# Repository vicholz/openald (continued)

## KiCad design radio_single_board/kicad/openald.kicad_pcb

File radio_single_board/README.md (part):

# OpenALD: PCB, assembly files and 3D-printed case (v1.0)

OpenALD is an ATmega328PB + RDA5807M (RRD-102 module) FM radio, **programmable over its USB-C port** (CH340K USB-serial, Arduino IDE / MiniCore). It runs from one 18650 cell (reverse-polarity protected), charges over USB-C (TP4056 + DW01A/FS8205A protection) and uses an XC6206 3.3 V LDO. Controls are a thumbwheel encoder with push for volume and tuning (**press the wheel = battery check**; there is no separate battery-check button any more), and a slide power switch that sticks out of the case. A **3-LED battery-level bar** runs as a **vertical column centred across the front face** near the jack end (so it stays well above the rim when the radio stands USB-C-down in the OpenALD Dock), and the TP4056 red/green charge LEDs sit next to the USB-C. The headphone cable acts as the antenna. The board silkscreen reads **OpenALD v1.0**.

> **Note:** I couldn't open the attached spec file on the build machine. This design follows the written summary of the spec instead, so compare it against your original.

> **OpenALD v1.0 is untested hardware.** This release is the former FM radio rev 4.3 design, renamed and reset to v1.0, with no electrical changes. Since then (all still v1.0): the level bar moved to a vertical column near the jack end for the charging dock, and on 2026-11-11 the separate battery-check button SW2 was removed (the wheel press does its job through a small P-FET, Q4) and the bar was centred across the board and moved up (see "Wheel press replaces the battery-check button"). On 2026-11-12 the USB-C receptacle J1 moved 0.9 mm toward the board edge and the case got the Feather's straight cable-plug recess plus assembly notches (see "USB-C 0.9 mm out to the case face"). It passes ERC, DRC and the 3D case-fit check. Pre-release rev 4.2 had two full datasheet reviews, and rev 4.3 (which only changed the charge-current resistor) had its own independent review (see "Pre-release history" below). No board has been built or programmed yet. Build one or two first.

> **t116u (2026-11-24, still v1.0): USB-C on the bottom END, centred — supersedes the side-USB envelope below.**
> Victor: "All boards except for the MI03 should have the USB-C connector in the same location at the bottom so they
> can be placed into the charging station for charging … Try to keep the single board 2 layer."
> * **Board 26.9 × 84.75 mm, still 2 layers** (was 25.5): J1 moved to the **bottom edge, centred** (shell 1.5 mm
>   past the edge); everything re-placed around it (holder + pin now toward the USB end, level bar D1/D5/D6 as a
>   column and the TP4056 charge LEDs D3/D4 at the top / jack end, wheel and switch on the right edge, jack top-left).
>   Re-routed with Freerouting: 983 track segments, 146 vias, 2.11 m; GND pours on both layers.
> * **Case 31.9 W × 89.75 L × 33.86 T** (front shell 9.85, back cover 24.01; thinner than the 34.83 side-USB case).
>   **USB-C in the bottom end face, centred across the width, 6.62 mm behind the front face, mouth 1.0 mm inside
>   the face**, 13.0 × 7.6 r 3 cable-plug recess — identical to the Feather radio, so both stand in the same dock
>   pocket (`../charging_dock/DOCK_INTERFACE.md`). Jack hole in the top end wall. Switch knob 2.8 mm and wheel
>   0.35 mm proud of the right side (above the pocket; t122u: no notch).
> * Checks: ERC 0 errors / 2 accepted warnings; **DRC 0 errors, 0 unconnected**, 82 silk-only (9 edge / 35 over
>   copper / 38 overlap); JLC CPL correction table OK; case fit **0 interferences** (closest LED tunnel: Q1, 0.25 mm).
>   JLC parts ≈ $7.32 / board. Fab outputs, vendor BOMs and previews regenerated.
> * The notes below (side USB-C, 25.5 mm board, 30.5 × 89.75 × 34.83 case) are history.
> * **t122u dock collar:** the Feather case grew to 35.9 wide, so the dock pockets are 35.9 × 33.86 now. This case
>   keeps its 31.9 body but its **lowest 27 mm (the part in the 25 mm pocket) is 35.9 wide**, 2 mm extra per side,
>   with a 2 mm 45° step back to the body (`dock_W`, `dock_collar_h` in `case/openald_case.scad`). The switch knob
>   and wheel are above the collar and unchanged. Outer bounding box 35.9 × 89.75 × 33.86; fit 0 interferences.

> **2026-11-24 unified envelope (still v1.0; supersedes the size, mounting, USB-C, LED and case notes further down,
> which are kept as history).** Victor asked for the single board and the Feather to match the MI03 case so all three
> use one charging dock. Changes:
> * **Board 25.5 × 84.75 mm, 2 layers**, 1.6 mm (was 38 × 87). A first cut at 22.5 mm wide only closed on 4 layers;
>   Victor then asked to make the board and cases "slightly bigger if it helps to keep the board 2 layers", so the
>   board was widened (length unchanged) and parts spread across the extra width (`placement.py`: J1 stays on the
>   left edge, wheel and switch on the right edge, holder centred). Freerouting on 2 layers: **24.5 and 25.0 mm left
>   3 unconnected nets** (U3 SCK/RX/TX area; 24.5 tried twice), **25.5 mm routed completely**, so 25.5 is the
>   smallest width found (0.5 mm steps). GND is routed as copper like every other net, and both layers carry GND
>   pours (islands removed) stitched with vias, so the ground is connected by tracks, not only by the pours. Same
>   schematic, same parts, BH-18650-PC holder kept.
> * **USB-C J1 moved to the left long edge**, centred 27.8 mm below the board's top end = **30.3 mm from the case's
>   top outer end, 7.55 mm behind the front face, mouth 1.0 mm inside the side face** (MI03 values), with the MI03
>   13.0 × 7.6 r 3 cable-plug recess. The radio docks **lying on that side**.
> * **Case 30.5 W × 89.75 L × 34.83 T** (was 43 × 92 × 33.4): same length, thickness, corners (r 5 / r 2) and USB-C
>   position as the MI03 case; 3 mm wider than the MI03 (27.5) because of the 2-layer board. Width is the height above
>   the pocket floor in the dock, so it uses the same pockets.
>   **Thickness grew 1.43 mm (33.4 → 34.83)**: the USB-C must sit 7.55 mm behind the front face like the MI03's,
>   and with the PCB at that depth the front shell is 10.78 mm tall; the holder under the board then needs 24.05 mm
>   behind it. Keeping 33.4 would have meant moving the MI03's USB-C, which Victor gave as the reference.
> * Level bar (D1/D5/D6) is now a row **across** the board near the top end (reads as a vertical bar when docked,
>   well above the pocket rim); the TP4056 charge LEDs D3/D4 sit beside it. Each has its own light tunnel.
> * Mounting: no more corner holes. The holder is screwed through its own two floor holes, a 0.8 mm printed
>   **holder spacer** and the PCB into two front-shell bosses (2 × M2 self-tapping). The **back cover snaps on**
>   (lip + 4 bumps), so the cell is changed without tools. The heat-set inserts and `case/nut_variant/` are gone.
> * Checks: ERC 0 errors / 2 accepted warnings; **DRC 0 errors, 0 unconnected**, 87 cosmetic silkscreen warnings (10
>   silk_edge_clearance, 33 silk_over_copper, 44 silk_overlap); JLC CPL correction table OK; case fit **0
>   interferences** (closest: Q4's LED tunnel, 0.40 mm); all three STLs watertight single bodies. 1360 track segments,
>   167 vias, 2.37 m of track.

The hardware in this v1.0 package is the ~900 mA charge-current design (R3 = 1.2k, TP4056 PROG). Charge time for a 3000 mAh 18650 is about 3.7 h if the chip holds 900 mA through the CC phase, likely closer to ~4 h in the closed case if the TP4056 thermally throttles. Use a **≥ 1 A charger**. A laptop USB 2.0 port is only rated 500 mA. If you need to charge from a laptop USB-A port, change **R3 to 2.4k (C22940, Basic) for ~460 mA**. See the pre-release rev 4.3 notes for the thermal estimate, USB source details, and the first-board cell-temperature check.

## Board at a glance
| | |
|---|---|
| Size | **26.9 x 84.75 mm**, 1.6 mm FR-4, 2 layers, 1 oz, 2.5 mm corner radius (t116u 2026-11-24; was 25.5 x 84.75, before that 38 x 87) |
| Mounting | No corner holes. 2x M2 self-tapping screws through the holder's two floor holes, the spacer and the PCB at (12.75, 17.62) and (12.75, 73.23) mm from the top-left corner into front-shell bosses |
| Top side | All SMT parts (including the 3 level-bar LEDs), plus the power switch (THT) and the hand-soldered RRD-102 module |
| Bottom side | MPD BH-18650-PC holder only (THT, hand-soldered) |
| Copper | 2026-11-24: GND routed by Freerouting like every other net, plus GND pours on F.Cu and B.Cu (islands removed) and stitching vias. Power nets 0.5 mm, signals 0.25 mm (0.15 mm minimum at the TQFP/ESSOP pins). 0.45 mm edge keep-out while routing. 1360 track segments, 167 vias, 2.37 m |
| ERC | **0 errors**, 2 accepted warnings (`fab/erc_report.txt`): pin_to_pin on U3 pins 3/6 (PE0 tied to GND, PE1 tied to +3V3 for ATmega328P-AU drop-in). This is intentional |
| DRC | **0 errors, 0 unconnected pads** (2026-11-24 2-layer re-route). 87 cosmetic silkscreen warnings are waived: 10 silk_edge_clearance (the jack, wheel, switch and USB-C overhang the edge on purpose), 33 silk_over_copper, 44 silk_overlap |

## How charging is shown (power switch off or on)
The power switch cuts VSYS. In rev 4 the MCU also runs from USB with the switch off (see "Power path"), so firmware can show the charging animation on its own while USB is plugged in (optional). The rev 3 options still work:
1. **Always, with no MCU needed:** the TP4056's own LEDs, **D3 red = charging and D4 green = full**, light from USB power. They shine through their own two light tunnels just left of the USB-C. This works with the switch off.
2. **With the switch off, hold the wheel pressed in:** the wheel's push switch turns on P-FET Q4, which powers the MCU from the battery (through D10, and VSYS through D2) for as long as the wheel is held in. While held, the MCU reads nCHRG and shows the charging animation or the level on the bar. Releasing the wheel powers it off again.
3. **With the switch on:** a short press of the wheel any time shows the level on the bar, or the charging animation if USB is charging. Plugging USB in while the radio is on also shows the charging animation once for 3 s.

Rev 4 powers the MCU from USB through its **own** LDO (U6) instead of feeding VBUS into VSYS. That way the FM module and the battery divider stay off. Note that while USB is powering the MCU with the switch off, BAT_ADC reads about 0 V, so the cell voltage isn't measurable then. For the level while charging, hold the wheel in (VSYS then sees the cell through Q4 and D2) or switch on.

## Part colours (t124u)
Victor: "make all 3 cases and their parts different colors so it is easy to tell the parts apart". Each case family has
its own hue (single board **blues**, Feather **greens**, MI03 **oranges / reds**, dock **purples**); this one uses
**blues**. The same colours are used in every preview and in the coloured 3MF plate **`case/openald_single_board_case_colored.3mf`** (all printed parts laid
out on one plate, each a separate named object with its colour; source `../tools/palette.py`, rebuilt by
`../tools/make_3mf.py`). Colours are only for telling the parts apart; print in any filament.

| Part (STL) | What | Colour | Hex |
|---|---|---|---|
| `case/case_top.stl` | front shell | blue | `#2E6FD8` |
| `case/case_bottom.stl` | back cover | light blue | `#9CC3F5` |
| `case/holder_spacer.stl` | holder spacer | navy | `#0B2E6B` |

## Files
```
kicad/                     KiCad 9 project (open openald.kicad_pro)
  openald.kicad_sch       schematic (PDF in docs/openald-schematic.pdf)
  openald.kicad_pcb       routed board
  openald.pretty/         custom footprints: RRD-102 module, Mitsumi SIQ-02FVS3, HRO SK-12E12-G5 switch (U3/U7/U8 use stock KiCad footprints)
  openald.kicad_sym       custom symbols;  openald.3dshapes/  simple 3D models for previews and the fit check
fab/
  openald-gerbers-jlcpcb.zip   Gerbers + Excellon drill files (upload this)
  openald-BOM-jlcpcb.csv       JLC assembly BOM (Comment, Designator, Footprint, LCSC Part #)
  openald-CPL-jlcpcb.csv       JLC pick-and-place (Designator, Mid X, Mid Y, Layer, Rotation), corrected for EasyEDA origins
  openald-centroid.csv         standard centroid / XY file (Designator, Comment, Footprint, Mid X, Mid Y, Rotation, Layer); same positions as the JLC CPL
  openald.pos                  KiCad ASCII position file (mm); same corrected positions as the centroid/CPL, plus hand-soldered U4 and BT1
  jlc_cpl_fit.json              per-part fit of the EasyEDA footprints (offsets, rotations, pad match)
  openald-BOM-human.csv        full BOM with MPNs, qty, live LCSC stock and price, links, plus hand-solder and off-board parts
  openald-BOM-pcbway.xlsx      PCBWay SMT assembly BOM (official template filled; qty per board; title says 5PCS)
  openald-BOM-nextpcb.xls      NextPCB assembly BOM (official template filled; qty per board)
  minimal/                      JLC files for a 4-part "hotplate" assembly only (see below)
    openald-BOM-jlcpcb-minimal.csv
    openald-CPL-jlcpcb-minimal.csv
    openald-centroid-minimal.csv
    openald-minimal.pos
    openald-LCSC-order-handsolder.csv   remaining LCSC parts for 5 boards, with labelled spares
    cost_estimate.txt
  erc_report.txt, drc_report.txt, lcsc_lookup.json, cost_summary.json
case/
  openald_case.scad       parametric OpenSCAD case (includes case_params.scad)
  case_params.scad         AUTO-GENERATED from the PCB by scripts/gen_case_params.py
  case_top.stl             front shell (PCB + holder screw into it)
  case_bottom.stl          snap-on back cover
  holder_spacer.stl        0.8 mm plate between the PCB and the holder
  case_fit_report.txt      3D interference check of the assembled PCB against both halves and the LED tunnel walls
previews/                  pcb_top.png, pcb_bottom.png, pcb_closeup_led_bar.png, pcb_closeup_reverse_polarity.png,
                           pcb_closeup_polarity_marks_bottom.png (rev 4.2), schematic-1.png, case_closed.png, case_*.png,
                           closeup_led_bar.png, closeup_front_usb_leds.png, cutaway_led_tunnels.png (section through the bar),
                           closeup_power_switch.png, closeup_usb_c.png, closeup_thumbwheel.png, closeup_jack_end.png,
                           cpl_overlay_<REF>.png (EasyEDA/JLC footprint vs KiCad pads; rev 4 adds U3/U6/U7/U8, rev 4.2 Q2/Q3, 2026-11-11 Q4),
                           pcb_closeup_usb_serial.png
docs/openald-schematic.pdf
scripts/                   generator scripts. run_all_pcb.sh regenerates everything up to DRC,
                           make_fab.py the fab outputs (add --minimal for the hotplate assembly set),
                           make_vendor_boms.py the PCBWay/NextPCB BOMs (templates in scripts/templates/),
                           build_case.sh the case, its checks and the renders
```

## Ordering at JLCPCB (assembled)
1. Upload `fab/openald-gerbers-jlcpcb.zip`. Settings: 2 layers, 26.9x84.75 mm, 1.6 mm, any colour, HASL (lead-free) or ENIG.
2. Turn on **PCB Assembly**, top side.
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
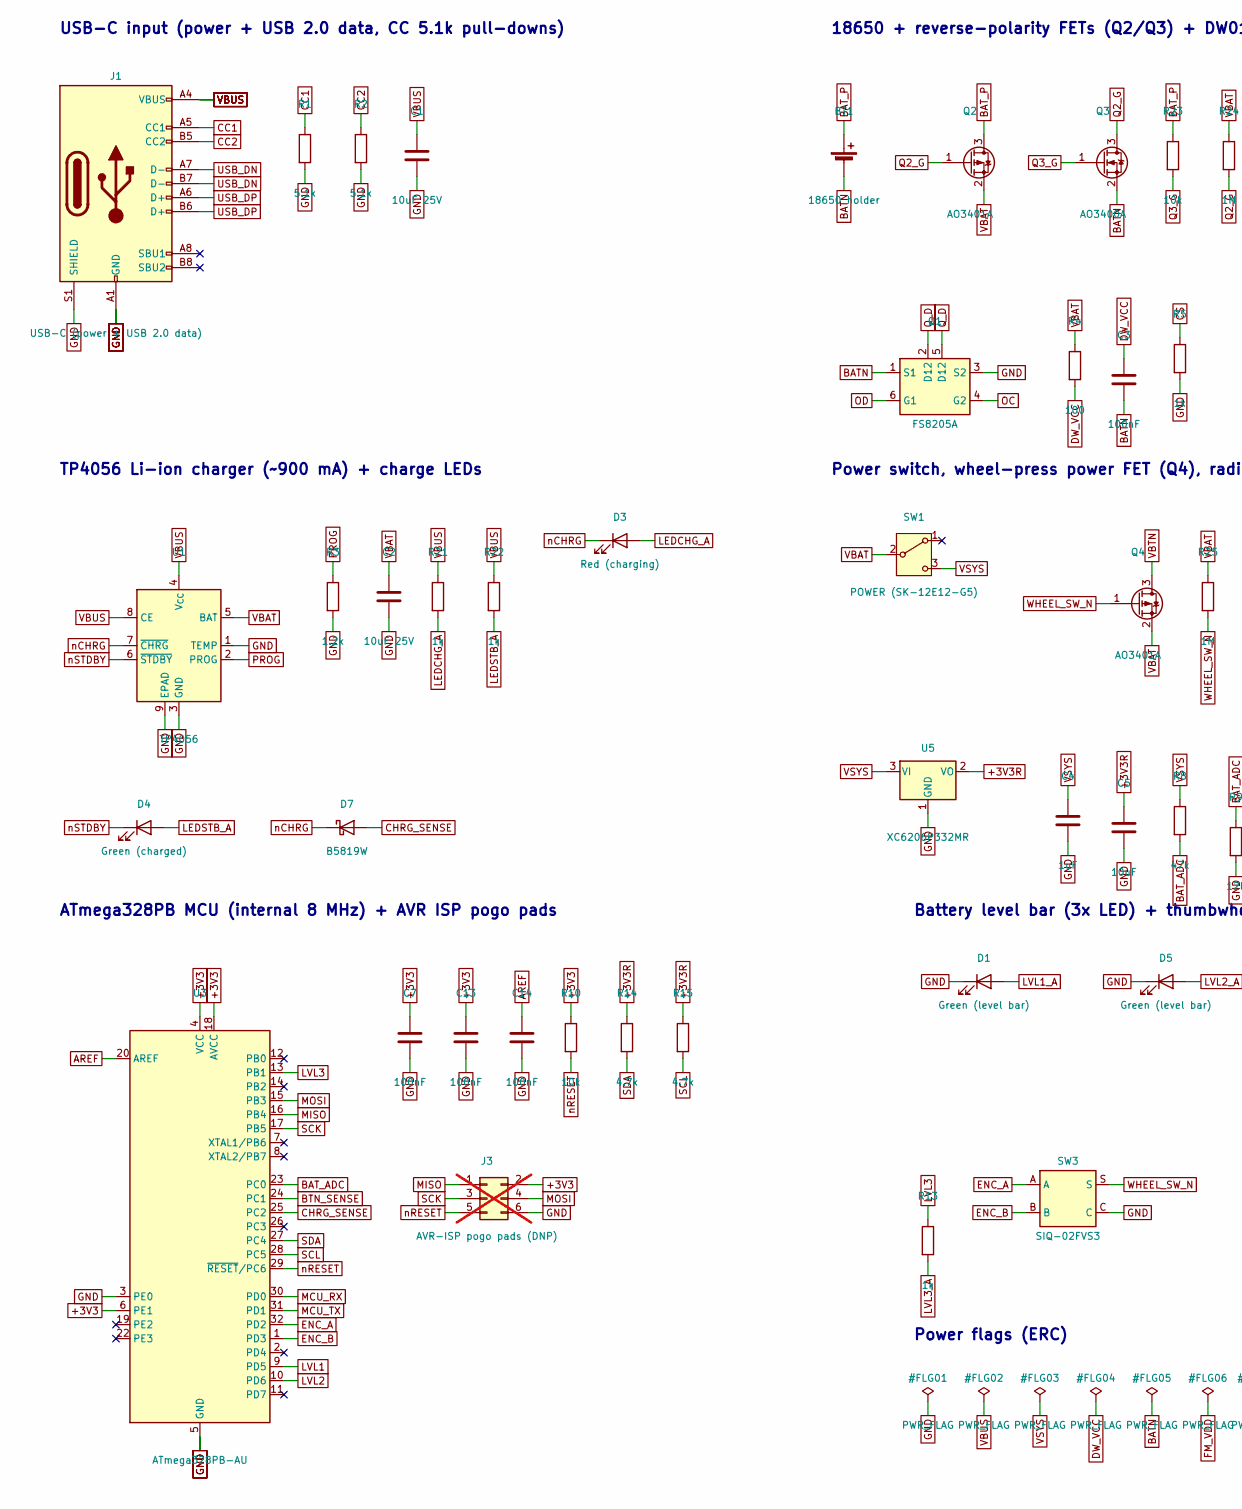
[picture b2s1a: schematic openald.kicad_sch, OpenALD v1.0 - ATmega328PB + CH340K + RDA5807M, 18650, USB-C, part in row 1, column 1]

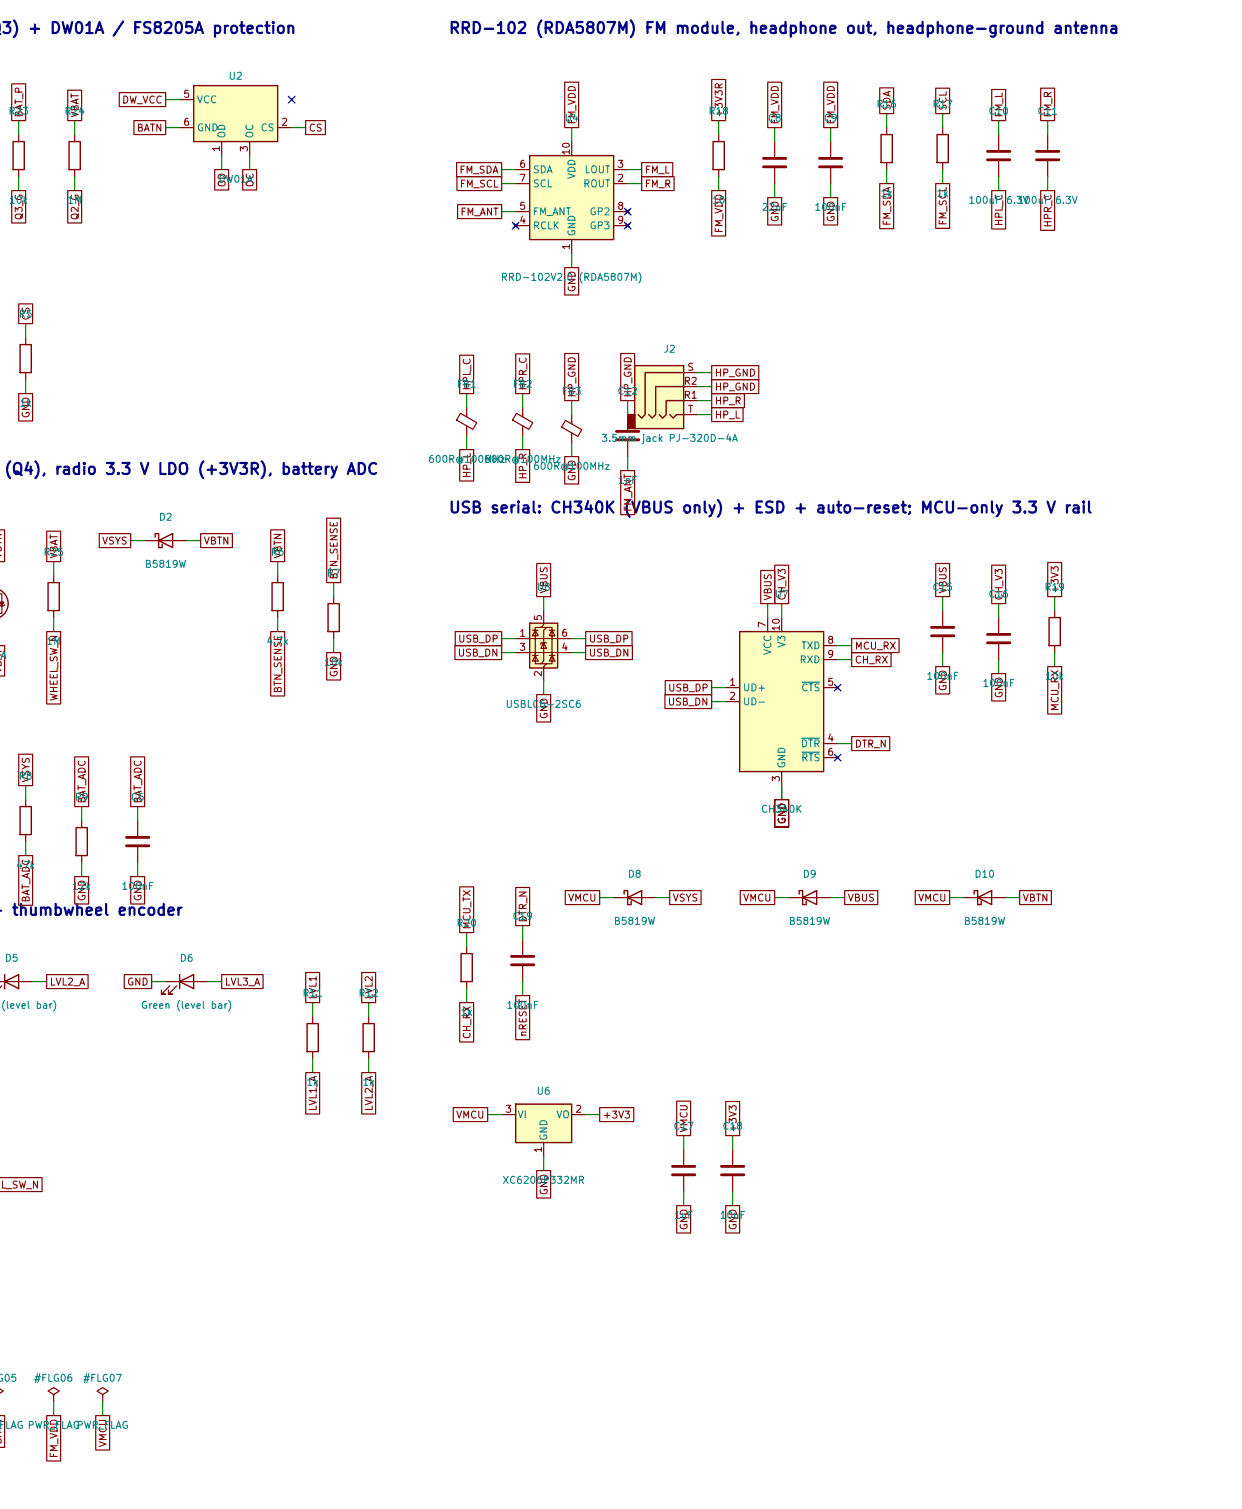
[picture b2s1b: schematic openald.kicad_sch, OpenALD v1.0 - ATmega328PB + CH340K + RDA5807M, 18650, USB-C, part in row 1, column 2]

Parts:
BT1: 18650 holder; BatteryHolder_MPD_BH-18650-PC; MPN MPD BH-18650-PC
C1, C2: 10uF 25V; C_0805_2012Metric; MPN CL21A106KAYNNNE; LCSC C15850
C3, C6, C7, C9, C13, C14, C15, C16, C19: 100nF; C_0603_1608Metric; MPN CC0603KRX7R9BB104; LCSC C14663
C4, C17: 1uF; C_0603_1608Metric; MPN CL10A105KB8NNNC; LCSC C15849
C5, C18: 10uF; C_0603_1608Metric; MPN CL10A106KP8NNNC; LCSC C19702
C8: 22uF; C_0805_2012Metric; MPN CL21A226MAQNNNE; LCSC C45783
C10, C11: 100uF 6.3V; C_1206_3216Metric; MPN CL31A107MQHNNNE; LCSC C15008
C12: 1nF; C_0603_1608Metric; MPN CL10B102KB8NNNC; LCSC C1588
D1, D5, D6: Green (level bar); LED_0603_1608Metric; MPN KT-0603G; LCSC C12624
D2, D7, D8, D9, D10: B5819W; D_SOD-123; MPN B5819W SL; LCSC C8598
D3: Red (charging); LED_0603_1608Metric; MPN KT-0603R; LCSC C2286
D4: Green (charged); LED_0603_1608Metric; MPN KT-0603G; LCSC C12624
FB1, FB2, FB3: 600R@100MHz; L_0603_1608Metric; MPN GZ1608D601TF; LCSC C1002
J1: USB-C (power + USB 2.0 data); USB_C_Receptacle_HRO_TYPE-C-31-M-12; MPN HRO TYPE-C-31-M-12; LCSC C165948
J2: 3.5mm jack PJ-320D-4A; Jack_3.5mm_KoreanHropartsElec_PJ-320D-4A_Horizontal; MPN HRO PJ-320D-4A; LCSC C95562
J3: AVR-ISP pogo pads (DNP); PinHeader_2x03_P2.54mm_Vertical; MPN 2x3 2.54mm header / pogo (DNP); not fitted
Q1: FS8205A; SOT-23-6; MPN FS8205A (TECH PUBLIC); LCSC C2830320
Q2, Q4: AO3401A; SOT-23; MPN AOS AO3401A; LCSC C15127
Q3: AO3400A; SOT-23; MPN AOS AO3400A; LCSC C20917
R1, R2: 5.1k; R_0603_1608Metric; MPN 0603WAF5101T5E; LCSC C23186
R3: 1.2k; R_0603_1608Metric; MPN 0603WAF1201T5E; LCSC C22765
R4: 100; R_0603_1608Metric; MPN 0603WAF1000T5E; LCSC C22775
R5, R11, R12, R13, R16, R17, R20, R21, R22: 1k; R_0603_1608Metric; MPN 0603WAF1001T5E; LCSC C21190
R6, R14, R15: 4.7k; R_0603_1608Metric; MPN 0603WAF4701T5E; LCSC C23162
R7, R10, R19, R23: 10k; R_0603_1608Metric; MPN 0603WAF1002T5E; LCSC C25804
R8: 47k; R_0603_1608Metric; MPN 0603WAF4702T5E; LCSC C25819
R9: 12k; R_0603_1608Metric; MPN 0603WAF1202T5E; LCSC C22790
R18: 10; R_0603_1608Metric; MPN 0603WAF100JT5E; LCSC C22859
R24, R25: 1M; R_0603_1608Metric; MPN 0603WAF1004T5E; LCSC C22935
SW1: POWER (SK-12E12-G5); SW_Slide_SPDT_Angled_HRO_SK-12E12-G5; MPN HRO SK-12E12-G5; LCSC C136720
SW3: SIQ-02FVS3; Mitsumi_SIQ-02FVS3; MPN Mitsumi SIQ-02FVS3; LCSC C2925423
U1: TP4056; SOIC-8-1EP_3.9x4.9mm_P1.27mm_EP2.41x3.3mm; MPN TP4056-42-ESOP8; LCSC C16581
U2: DW01A; SOT-23-6; MPN DW01A (PUOLOP); LCSC C351410
U3: ATmega328PB-AU; TQFP-32_7x7mm_P0.8mm; MPN ATMEGA328PB-AU; LCSC C132230
U4: RRD-102V2.0 (RDA5807M); RRD-102_RDA5807M_Module; MPN RRD-102V2.0 RDA5807M module
U5, U6: XC6206P332MR; SOT-23-3; MPN XC6206P332MR-G; LCSC C5446
U7: CH340K; SSOP-10-1EP_3.9x4.9mm_P1mm_EP2.1x3.3mm; MPN WCH CH340K; LCSC C968586
U8: USBLC6-2SC6; SOT-23-6; MPN ST USBLC6-2SC6; LCSC C7519

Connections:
+3V3: C7.1, C13.1, C18.1, J3.2, R10.1, R19.1, U3.4 (VCC), U3.6 (PE1), U3.18 (AVCC), U6.2 (VO)
+3V3R: C5.1, R14.1, R15.1, R18.1, U5.2 (VO)
AREF: C14.1, U3.20 (AREF)
BATN: BT1.2 (-), C3.2, Q1.1 (S1), Q3.2 (S), U2.6 (GND)
BAT_ADC: C6.1, R8.2, R9.1, U3.23 (PC0)
BAT_P: BT1.1 (+), Q2.3 (D), R23.1
BTN_SENSE: R6.2, R7.1, U3.24 (PC1)
CC1: J1.A5 (CC1), R1.1
CC2: J1.B5 (CC2), R2.1
CHRG_SENSE: D7.2 (A), U3.25 (PC2)
CH_RX: R20.2, U7.9 (RXD)
CH_V3: C16.1, U7.10 (V3)
CS: R5.1, U2.2 (CS)
DTR_N: C19.1, U7.4 (~DTR)
DW_VCC: C3.1, R4.2, U2.5 (VCC)
ENC_A: SW3.A, U3.32 (PD2)
ENC_B: SW3.B, U3.1 (PD3)
FM_ANT: C12.2, U4.5 (FM_ANT)
FM_L: C10.1, U4.3 (LOUT)
FM_R: C11.1, U4.2 (ROUT)
FM_SCL: R17.2, U4.7 (SCL)
FM_SDA: R16.2, U4.6 (SDA)
FM_VDD: C8.1, C9.1, R18.2, U4.10 (VDD)
GND: C1.2, C2.2, C4.2, C5.2, C6.2, C7.2, C8.2, C9.2, C13.2, C14.2, C15.2, C16.2, C17.2, C18.2, D1.1 (K), D5.1 (K), D6.1 (K), FB3.2, J1.A1 (GND), J1.A12 (GND), J1.B1 (GND), J1.B12 (GND), J1.S1 (SHIELD), J3.6, Q1.3 (S2), R1.2, R2.2, R3.2, R5.2, R7.2, R9.2, SW3.C, U1.1 (TEMP), U1.3 (GND), U1.9 (EPAD), U3.3 (PE0), U3.5 (GND), U3.21 (GND), U4.1 (GND), U5.1 (GND), U6.1 (GND), U7.3 (GND), U7.11 (GND), U8.2 (GND)
HPL_C: C10.2, FB1.1
HPR_C: C11.2, FB2.1
HP_GND: C12.1, FB3.1, J2.R2, J2.S
HP_L: FB1.2, J2.T
HP_R: FB2.2, J2.R1
LEDCHG_A: D3.2 (A), R21.2
LEDSTB_A: D4.2 (A), R22.2
LVL1: R11.1, U3.9 (PD5)
LVL1_A: D1.2 (A), R11.2
LVL2: R12.1, U3.10 (PD6)
LVL2_A: D5.2 (A), R12.2
LVL3: R13.1, U3.13 (PB1)
LVL3_A: D6.2 (A), R13.2
MCU_RX: R19.2, U3.30 (PD0), U7.8 (TXD)
MCU_TX: R20.1, U3.31 (PD1)
MISO: J3.1, U3.16 (PB4)
MOSI: J3.4, U3.15 (PB3)
OC: Q1.4 (G2), U2.3 (OC)
OD: Q1.6 (G1), U2.1 (OD)
PROG: R3.1, U1.2 (PROG)
Q2_G: Q2.1 (G), Q3.3 (D), R24.2
Q3_G: Q3.1 (G), R23.2
Q_D: Q1.2 (D12), Q1.5 (D12)
SCK: J3.3, U3.17 (PB5)
SCL: R15.2, R17.1, U3.28 (PC5)
SDA: R14.2, R16.1, U3.27 (PC4)
USB_DN: J1.A7 (D-), J1.B7 (D-), U7.2 (UD-), U8.3 (I/O2), U8.4 (I/O2)
USB_DP: J1.A6 (D+), J1.B6 (D+), U7.1 (UD+), U8.1 (I/O1), U8.6 (I/O1)
VBAT: C2.1, Q2.2 (S), Q4.2 (S), R4.1, R24.1, R25.1, SW1.2 (B), U1.5 (BAT)
VBTN: D2.2 (A), D10.2 (A), Q4.3 (D), R6.1
VBUS: C1.1, C15.1, D9.2 (A), J1.A4 (VBUS), J1.A9 (VBUS), J1.B4 (VBUS), J1.B9 (VBUS), R21.1, R22.1, U1.4 (V_{CC}), U1.8 (CE), U7.7 (VCC), U8.5 (VBUS)
VMCU: C17.1, D8.1 (K), D9.1 (K), D10.1 (K), U6.3 (VI)
VSYS: C4.1, D2.1 (K), D8.2 (A), R8.1, SW1.3 (C), U5.3 (VI)
WHEEL_SW_N: Q4.1 (G), R25.2, SW3.S
nCHRG: D3.1 (K), D7.1 (K), U1.7 (~CHRG)
nRESET: C19.2, J3.5, R10.2, U3.29 (~RESET/PC6)
nSTDBY: D4.1 (K), U1.6 (~STDBY)

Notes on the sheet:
USB-C input (power + USB 2.0 data, CC 5.1k pull-downs)
TP4056 Li-ion charger (~900 mA) + charge LEDs
18650 + reverse-polarity FETs (Q2/Q3) + DW01A / FS8205A protection
Power switch, wheel-press power FET (Q4), radio 3.3 V LDO (+3V3R), battery ADC
ATmega328PB MCU (internal 8 MHz) + AVR ISP pogo pads
Battery level bar (3x LED) + thumbwheel encoder
RRD-102 (RDA5807M) FM module, headphone out, headphone-ground antenna
USB serial: CH340K (VBUS only) + ESD + auto-reset; MCU-only 3.3 V rail
Power flags (ERC)

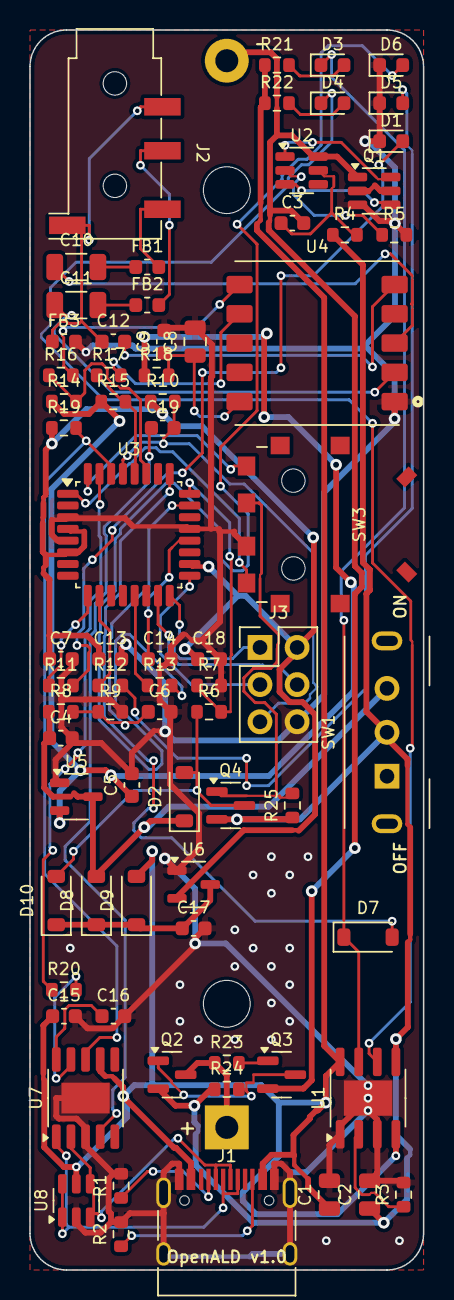
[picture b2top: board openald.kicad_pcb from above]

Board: 2 copper layers, 26.9 x 84.8 mm, 75 parts (1 on the bottom side), 61 nets.

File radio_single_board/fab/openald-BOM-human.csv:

Designator(s),Qty/board,Value / description,Manufacturer part,LCSC #,JLC library,LCSC stock (live),Unit price USD (qty 10),Assembly,Link
J1,1,USB-C (power + USB 2.0 data) (USB_C_Receptacle_HRO_TYPE-C-31-M-12),HRO TYPE-C-31-M-12,C165948,Extended,281632,0.1868,JLCPCB SMT,https://www.lcsc.com/product-detail/C165948.html
"R1,R2",2,5.1k (R_0603_1608Metric),0603WAF5101T5E,C23186,Basic,19705142,0.0015,JLCPCB SMT,https://www.lcsc.com/product-detail/C23186.html
"C1,C2",2,10uF 25V (C_0805_2012Metric),CL21A106KAYNNNE,C15850,Basic,8635577,0.0315,JLCPCB SMT,https://www.lcsc.com/product-detail/C15850.html
U1,1,TP4056 (SOIC-8-1EP_3.9x4.9mm_P1.27mm_EP2.41x3.3mm),TP4056-42-ESOP8,C16581,Preferred ext.,89499,0.1852,JLCPCB SMT,https://www.lcsc.com/product-detail/C16581.html
R3,1,1.2k (R_0603_1608Metric),0603WAF1201T5E,C22765,Basic,2122275,0.0034,JLCPCB SMT,https://www.lcsc.com/product-detail/C22765.html
"R5,R11,R12,R13,R16,R17,R20,R21,R22",9,1k (R_0603_1608Metric),0603WAF1001T5E,C21190,Basic,25689733,0.0017,JLCPCB SMT,https://www.lcsc.com/product-detail/C21190.html
D3,1,Red (charging) (LED_0603_1608Metric),KT-0603R,C2286,Basic,6046029,0.0077,JLCPCB SMT,https://www.lcsc.com/product-detail/C2286.html
"D1,D4,D5,D6",4,Green (charged) / Green (level bar) (LED_0603_1608Metric),KT-0603G,C12624,Extended,296191,0.0119,JLCPCB SMT,https://www.lcsc.com/product-detail/C12624.html
"Q2,Q4",2,AO3401A (SOT-23),AOS AO3401A,C15127,Basic,1606758,0.0813,JLCPCB SMT,https://www.lcsc.com/product-detail/C15127.html
Q3,1,AO3400A (SOT-23),AOS AO3400A,C20917,Basic,916553,0.0802,JLCPCB SMT,https://www.lcsc.com/product-detail/C20917.html
"R7,R10,R19,R23",4,10k (R_0603_1608Metric),0603WAF1002T5E,C25804,Basic,43282059,0.0022,JLCPCB SMT,https://www.lcsc.com/product-detail/C25804.html
"R24,R25",2,1M (R_0603_1608Metric),0603WAF1004T5E,C22935,Basic,3921133,0.0018,JLCPCB SMT,https://www.lcsc.com/product-detail/C22935.html
U2,1,DW01A (SOT-23-6),DW01A (PUOLOP),C351410,Extended,92420,0.0532,JLCPCB SMT,https://www.lcsc.com/product-detail/C351410.html
Q1,1,FS8205A (SOT-23-6),FS8205A (TECH PUBLIC),C2830320,Extended,185458,0.0499,JLCPCB SMT,https://www.lcsc.com/product-detail/C2830320.html
R4,1,100 (R_0603_1608Metric),0603WAF1000T5E,C22775,Basic,9994733,0.002,JLCPCB SMT,https://www.lcsc.com/product-detail/C22775.html
"C3,C6,C7,C9,C13,C14,C15,C16,C19",9,100nF (C_0603_1608Metric),CC0603KRX7R9BB104,C14663,Basic,37482941,0.006,JLCPCB SMT,https://www.lcsc.com/product-detail/C14663.html
SW1,1,POWER (SK-12E12-G5) (SW_Slide_SPDT_Angled_HRO_SK-12E12-G5),HRO SK-12E12-G5,C136720,Extended,15487,0.1132,JLCPCB THT (Standard PCBA) - or delete the BOM line and hand-solder,https://www.lcsc.com/product-detail/C136720.html
"D2,D7,D8,D9,D10",5,B5819W (D_SOD-123),B5819W SL,C8598,Basic,377359,0.0262,JLCPCB SMT,https://www.lcsc.com/product-detail/C8598.html
"R6,R14,R15",3,4.7k (R_0603_1608Metric),0603WAF4701T5E,C23162,Basic,14768971,0.0028,JLCPCB SMT,https://www.lcsc.com/product-detail/C23162.html
"U5,U6",2,XC6206P332MR (SOT-23-3),XC6206P332MR-G,C5446,Basic,479522,0.1262,JLCPCB SMT,https://www.lcsc.com/product-detail/C5446.html
"C4,C17",2,1uF (C_0603_1608Metric),CL10A105KB8NNNC,C15849,Basic,12249102,0.0113,JLCPCB SMT,https://www.lcsc.com/product-detail/C15849.html
"C5,C18",2,10uF (C_0603_1608Metric),CL10A106KP8NNNC,C19702,Basic,9405851,0.0233,JLCPCB SMT,https://www.lcsc.com/product-detail/C19702.html
R8,1,47k (R_0603_1608Metric),0603WAF4702T5E,C25819,Basic,2902592,0.0016,JLCPCB SMT,https://www.lcsc.com/product-detail/C25819.html
R9,1,12k (R_0603_1608Metric),0603WAF1202T5E,C22790,Basic,1062704,0.0031,JLCPCB SMT,https://www.lcsc.com/product-detail/C22790.html
U3,1,ATmega328PB-AU (TQFP-32_7x7mm_P0.8mm),ATMEGA328PB-AU,C132230,Extended,565,1.5882,JLCPCB SMT,https://www.lcsc.com/product-detail/C132230.html
U8,1,USBLC6-2SC6 (SOT-23-6),ST USBLC6-2SC6,C7519,Extended,22712,0.1559,JLCPCB SMT,https://www.lcsc.com/product-detail/C7519.html
U7,1,CH340K (SSOP-10-1EP_3.9x4.9mm_P1mm_EP2.1x3.3mm),WCH CH340K,C968586,Extended,30951,0.5464,JLCPCB SMT,https://www.lcsc.com/product-detail/C968586.html
SW3,1,SIQ-02FVS3 (Mitsumi_SIQ-02FVS3),Mitsumi SIQ-02FVS3,C2925423,Extended,1290,3.0374,JLCPCB SMT,https://www.lcsc.com/product-detail/C2925423.html
R18,1,10 (R_0603_1608Metric),0603WAF100JT5E,C22859,Basic,5524270,0.002,JLCPCB SMT,https://www.lcsc.com/product-detail/C22859.html
C8,1,22uF (C_0805_2012Metric),CL21A226MAQNNNE,C45783,Basic,4143825,0.1055,JLCPCB SMT,https://www.lcsc.com/product-detail/C45783.html
"C10,C11",2,100uF 6.3V (C_1206_3216Metric),CL31A107MQHNNNE,C15008,Basic,1561175,0.109,JLCPCB SMT,https://www.lcsc.com/product-detail/C15008.html
"FB1,FB2,FB3",3,600R@100MHz (L_0603_1608Metric),GZ1608D601TF,C1002,Basic,403719,0.0115,JLCPCB SMT,https://www.lcsc.com/product-detail/C1002.html
C12,1,1nF (C_0603_1608Metric),CL10B102KB8NNNC,C1588,Basic,5973452,0.0082,JLCPCB SMT,https://www.lcsc.com/product-detail/C1588.html
J2,1,3.5mm jack PJ-320D-4A (Jack_3.5mm_KoreanHropartsElec_PJ-320D-4A_Horizontal),HRO PJ-320D-4A,C95562,Extended,973,0.1216,JLCPCB SMT,https://www.lcsc.com/product-detail/C95562.html
U4,1,RRD-102V2.0 RDA5807M FM module (11x11mm castellated),RRD-102V2.0 RDA5807M module,,—,—,~$1-2 ea (often sold in 5-10 packs),Hand solder,https://www.amazon.com/s?k=RDA5807M+RRD-102+FM+module
BT1,1,"MPD BH-18650-PC 18650 PCB holder (THT, 2 pins 72.9mm)",MPD BH-18650-PC,,—,—,~$3,Hand solder,https://www.digikey.com/en/products/result?keywords=BH-18650-PC
J3,1,"2x3 2.54mm AVR-ISP pogo pads (ATmega328PB MISO/SCK/MOSI/RESET, 3.3 V) - bootloader burn only; do not leave a header fitted",2x3 2.54mm header / pogo (DNP),,—,—,~$0.10 (or a 2x3 pogo clip),DNP,https://www.digikey.com/en/products/result?keywords=2x3%20pi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
—,1,18650 Li-ion cell (flat or button top; protected cells up to ~69mm fit the MPD holder),,,,,~$5,Off-board,https://www.amazon.com/s?k=18650+battery
—,2,"M2 x 8-10 mm self-tapping pan-head screws (through the holder floor holes, spacer and PCB into the front-shell bosses; 1.7 mm pilot 7.2 mm deep; holder floor thickness not verified)",,,,,~$0.05,Off-board,https://www.amazon.com/s?k=M2+self+tapping+screws+pan+head

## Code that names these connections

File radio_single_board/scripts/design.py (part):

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P+=[R("R1","5.1k","C23186","CC1","GND","usb","0603WAF5101T5E"), R("R2","5.1k","C23186","CC2","GND","usb","0603WAF5101T5E"),
    C("C1","10uF 25V","C15850","VBUS","GND","usb",C0805,"CL21A106KAYNNNE")]
P+=[dict(ref="U1",lib="Battery_Management:TP4056-42-ESOP8",val="TP4056",fp="Package_SO:SOIC-8-1EP_3.9x4.9mm_P1.27mm_EP2.41x3.3mm",lcsc="C16581",mpn="TP4056-42-ESOP8",grp="chg",
        pins={"1":"GND","2":"PROG","3":"GND","4":"VBUS","5":"VBAT","6":"nSTDBY","7":"nCHRG","8":"VBUS","9":"GND"})]
P+=[R("R3","1.2k","C22765","PROG","GND","chg","0603WAF1201T5E"),
    C("C2","10uF 25V","C15850","VBAT","GND","chg",C0805,"CL21A106KAYNNNE"),
    R("R21","1k","C21190","VBUS","LEDCHG_A","chg","0603WAF1001T5E"), R("R22","1k","C21190","VBUS","LEDSTB_A","chg","0603WAF1001T5E"),
    dict(ref="D3",lib="Device:LED",val="Red (charging)",fp="LED_SMD:LED_0603_1608Metric",lcsc="C2286",mpn="KT-0603R",grp="chg",pins={"1":"nCHRG","2":"LEDCHG_A"}),
    dict(ref="D4",lib="Device:LED",val="Green (charged)",fp="LED_SMD:LED_0603_1608Metric",lcsc="C12624",mpn="KT-0603G",grp="chg",pins={"1":"nSTDBY","2":"LEDSTB_A"})]
# ---------------- 18650 + DW01A/FS8205A protection ----------------
P+=[dict(ref="BT1",lib="Device:Battery_Cell",val="18650 holder",fp="Battery:BatteryHolder_MPD_BH-18650-PC",lcsc="",mpn="MPD BH-18650-PC",grp="bat",side="B",
        pins={"1":"BAT_P","2":"BATN"},hand=True)]
# ---------------- rev 4.2: reverse-polarity protection (high-side P-FET, gated by an orientation-sensing N-FET) ----------------
# Q2 (AO3401A) sits between the holder + contact (BAT_P) and every other battery node (VBAT: TP4056 BAT, DW01A VCC via R4,
# SW1, Q4, C2).  Q3 (AO3400A) senses the cell itself: its gate sees BAT_P and its source BATN (cell -), so it is on only
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# gate at its source -> Q2 off and its body diode (anode BAT_P) is reverse biased, so no loop through the board exists,
# even with USB plugged in (TP4056 driving VBAT cannot turn Q2 on, because Q3 does not look at VBAT).
P+=[dict(ref="Q2",lib="Transistor_FET:AO3401A",val="AO3401A",fp="Package_TO_SOT_SMD:SOT-23",lcsc="C15127",mpn="AOS AO3401A",grp="bat",
        pins={"1":"Q2_G","2":"VBAT","3":"BAT_P"}),
    dict(ref="Q3",lib="Transistor_FET:AO3400A",val="AO3400A",fp="Package_TO_SOT_SMD:SOT-23",lcsc="C20917",mpn="AOS AO3400A",grp="bat",
        pins={"1":"Q3_G","2":"BATN","3":"Q2_G"}),
    R("R23","10k","C25804","BAT_P","Q3_G","bat","0603WAF1002T5E"),     # Q3 gate resistor (no DC current)
    R("R24","1M","C22935","VBAT","Q2_G","bat","0603WAF1004T5E")]      # Q2 gate pull-up to its source (~4 uA while Q3 is on)
P+=[dict(ref="U2",lib="Battery_Management:DW01A",val="DW01A",fp="Package_TO_SOT_SMD:SOT-23-6",lcsc="C351410",mpn="DW01A (PUOLOP)",grp="bat",
        pins={"1":"OD","2":"CS","3":"OC","4":None,"5":"DW_VCC","6":"BATN"}),
    dict(ref="Q1",lib="openald:FS8205A",val="FS8205A",fp="Package_TO_SOT_SMD:SOT-23-6",lcsc="C2830320",mpn="FS8205A (TECH PUBLIC)",grp="bat",
        pins={"1":"BATN","2":"Q_D","3":"GND","4":"OC","5":"Q_D","6":"OD"}),
    R("R4","100","C22775","VBAT","DW_VCC","bat","0603WAF1000T5E"),
    C("C3","100nF","C14663","DW_VCC","BATN","bat",mpn="CC0603KRX7R9BB104"),
    R("R5","1k","C21190","CS","GND","bat","0603WAF1001T5E")]
# ---------------- power switch, wheel-press power path (Q4), LDO ----------------
P+=[dict(ref="SW1",lib="Switch:SW_SPDT",val="POWER (SK-12E12-G5)",fp="openald:SW_Slide_SPDT_Angled_HRO_SK-12E12-G5",lcsc="C136720",mpn="HRO SK-12E12-G5",grp="pwr",tht=True,
        pins={"1":None,"2":"VBAT","3":"VSYS"}),
    # v1.0 wheel-press update (2026-11-11): the separate battery-check button SW2 (EVQ-P7A01P, C79167) is gone. The
    # thumbwheel's push switch (SW3 S -> C = GND) now does its job: R25 holds WHEEL_SW_N (Q4 gate) at VBAT, pressing the
    # wheel pulls it to GND, P-FET Q4 turns on and drives VBTN from VBAT exactly like SW2 did (D2 -> VSYS, D10 -> VMCU,
    # R6/R7 -> BTN_SENSE). So "hold the wheel in with the switch off" still powers the MCU for the battery check, and
    # with the switch on the MCU reads every wheel press on BTN_SENSE (PC1). Released: no current (gate at source).
    # Pressed: 4.2 uA in R25. PD4 is no longer connected (WHEEL_SW_N sits at VBAT, up to 4.2 V, too high for a 3.3 V pin).
    dict(ref="Q4",lib="Transistor_FET:AO3401A",val="AO3401A",fp="Package_TO_SOT_SMD:SOT-23",lcsc="C15127",mpn="AOS AO3401A",grp="pwr",
        pins={"1":"WHEEL_SW_N","2":"VBAT","3":"VBTN"}),   # AO3401A SOT-23: 1 G, 2 S, 3 D (same as Q2)
    R("R25","1M","C22935","VBAT","WHEEL_SW_N","pwr","0603WAF1004T5E"),
    dict(ref="D2",lib="Device:D_Schottky",val="B5819W",fp="Diode_SMD:D_SOD-123",lcsc="C8598",mpn="B5819W SL",grp="pwr",pins={"1":"VSYS","2":"VBTN"}),
    # rev 4.1: 4.7k/10k (was 47k/100k). VBTN floats when SW2 (now Q4) is open, and D2/D10 (B5819W) reverse leakage (JSCJ datasheet:
    # ~5 uA each at 25 C, ~10x at 75 C) into 147k gave ~1 V on PC1 at room temperature (above VIL max) -> false "pressed".
    R("R6","4.7k","C23162","VBTN","BTN_SENSE","pwr","0603WAF4701T5E"), R("R7","10k","C25804","BTN_SENSE","GND","pwr","0603WAF1002T5E"),
    dict(ref="U5",lib="Regulator_Linear:XC6206PxxxMR",val="XC6206P332MR",fp="Package_TO_SOT_SMD:SOT-23-3",lcsc="C5446",mpn="XC6206P332MR-G",grp="pwr",
        pins={"1":"GND","2":"+3V3R","3":"VSYS"}),
    C("C4","1uF","C15849","VSYS","GND","pwr",mpn="CL10A105KB8NNNC"), C("C5","10uF","C19702","+3V3R","GND","pwr",mpn="CL10A106KP8NNNC"),
    # rev 4.1: 47k/12k (was 100k/33k). 100k/33k put a full cell (4.24 V max) at 1.05 V, above the 1.0 V minimum of the
    # ATmega328PB internal 1.1 V reference (DS40001906 VINT 1.0-1.2 V) -> ADC could clip. Now 0.86 V; source 9.6k (<10k per DS).
    R("R8","47k","C25819","VSYS","BAT_ADC","pwr","0603WAF4702T5E"), R("R9","12k","C22790","BAT_ADC","GND","pwr","0603WAF1202T5E"),
    C("C6","100nF","C14663","BAT_ADC","GND","pwr",mpn="CC0603KRX7R9BB104")]
# ---------------- MCU: ATmega328PB-AU (TQFP-32), internal 8 MHz RC; Arduino (MiniCore) pin names in comments ----------------
# Pin 3 (PE0) is tied to GND and pin 6 (PE1) to +3V3 so an ATmega328P-AU (pin 3 = GND, pin 6 = VCC) also drops in;
# firmware must leave PE0/PE1 as inputs without pull-ups (Microchip AN42559 / AT15007).
P+=[dict(ref="U3",lib="MCU_Microchip_ATmega:ATmega328PB-A",val="ATmega328PB-AU",fp="Package_QFP:TQFP-32_7x7mm_P0.8mm",lcsc="C132230",mpn="ATMEGA328PB-AU",grp="mcu",
        pins={"4":"+3V3","18":"+3V3","6":"+3V3","5":"GND","21":"GND","3":"GND","20":"AREF",
              "32":"ENC_A","1":"ENC_B","2":None,                     # PD2/INT0 (D2), PD3/INT1 (D3), PD4 (D4) spare: wheel press is read on BTN_SENSE (PC1)
              "9":"LVL1","10":"LVL2","13":"LVL3",                    # PD5/OC0B (D5), PD6/OC0A (D6), PB1/OC1A (D9): hardware PWM
              "15":"MOSI","16":"MISO","17":"SCK",                    # PB3/PB4/PB5 (D11/D12/D13): ISP only
              "23":"BAT_ADC","24":"BTN_SENSE","25":"CHRG_SENSE",     # PC0/ADC0 (A0), PC1 (A1), PC2 (A2)
              "27":"SDA","28":"SCL","29":"nRESET",                   # PC4/SDA0 (A4), PC5/SCL0 (A5), PC6/RESET
              "30":"MCU_RX","31":"MCU_TX",                           # PD0/RXD0 (D0), PD1/TXD0 (D1)
              "7":None,"8":None,"11":None,"12":None,"14":None,"19":None,"22":None,"26":None}),
    C("C7","100nF","C14663","+3V3","GND","mcu",mpn="CC0603KRX7R9BB104"),     # VCC pin 4
    C("C13","100nF","C14663","+3V3","GND","mcu",mpn="CC0603KRX7R9BB104"),    # AVCC pin 18
    C("C14","100nF","C14663","AREF","GND","mcu",mpn="CC0603KRX7R9BB104"),    # AREF pin 20 (internal 1.1 V reference)
    # TP4056 nCHRG -> PC2 through a Schottky (cathode at nCHRG): reads low only while charging; blocks back-feed into an unpowered MCU
    dict(ref="D7",lib="Device:D_Schottky",val="B5819W",fp="Diode_SMD:D_SOD-123",lcsc="C8598",mpn="B5819W SL",grp="chg",pins={"1":"nCHRG","2":"CHRG_SENSE"}),
    R("R10","10k","C25804","+3V3","nRESET","mcu","0603WAF1002T5E"),
    # I2C pull-ups go to the radio rail: with the radio unpowered (switch off, USB in) they cannot back-feed the RDA5807M
    R("R14","4.7k","C23162","+3V3R","SDA","mcu","0603WAF4701T5E"), R("R15","4.7k","C23162","+3V3R","SCL","mcu","0603WAF4701T5E"),
    dict(ref="J3",lib="Connector_Generic:Conn_02x03_Odd_Even",val="AVR-ISP pogo pads (DNP)",fp="Connector_PinHeader_2.54mm:PinHeader_2x03_P2.54mm_Vertical",lcsc="",mpn="2x3 2.54mm header / pogo (DNP)",grp="mcu",
        pins={"1":"MISO","2":"+3V3","3":"SCK","4":"MOSI","5":"nRESET","6":"GND"},dnp=True)]
# ---------------- USB serial (CH340K, powered from VBUS only) + Arduino auto-reset + MCU-only 3.3 V rail ----------------
P+=[dict(ref="U8",lib="Power_Protection:USBLC6-2SC6",val="USBLC6-2SC6",fp="Package_TO_SOT_SMD:SOT-23-6",lcsc="C7519",mpn="ST USBLC6-2SC6",grp="ser",
        pins={"1":"USB_DP","6":"USB_DP","3":"USB_DN","4":"USB_DN","5":"VBUS","2":"GND"}),
    dict(ref="U7",lib="Interface_USB:CH340K",val="CH340K",fp="Package_SO:SSOP-10-1EP_3.9x4.9mm_P1mm_EP2.1x3.3mm",lcsc="C968586",mpn="WCH CH340K",grp="ser",
        pins={"1":"USB_DP","2":"USB_DN","3":"GND","11":"GND","7":"VBUS","10":"CH_V3","8":"MCU_RX","9":"CH_RX","4":"DTR_N","5":None,"6":None}),
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
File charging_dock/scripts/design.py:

"""OpenALD Dock v1.0 - parts, values, footprints, LCSC numbers and pin->net connections (single source of truth).
Power path: USB-C in (J1) -> F1 4 A fuse -> D1 SMBJ22A TVS -> Q1 AO4407A P-FET (gated by U1 HUSB238 PD sink, opens on
no-PD/OVP) -> VIN_SW -> 2x SY8205FCC 5 A buck (U2 -> 5V_A, U3 -> 5V_B, 5.10 V, enabled only above ~12 V) -> 6x SY6280AAC
current-limited switches (~1.45 A each) -> 6 vertical USB-C plugs (J2-J7)."""
R0603="Resistor_SMD:R_0603_1608Metric"; R0805="Resistor_SMD:R_0805_2012Metric"; C0603="Capacitor_SMD:C_0603_1608Metric"
C0805="Capacitor_SMD:C_0805_2012Metric"; C1206="Capacitor_SMD:C_1206_3216Metric"
def R(ref,val,lcsc,n1,n2,grp,mpn="",fp=R0603):
    return dict(ref=ref,lib="Device:R",val=val,fp=fp,lcsc=lcsc,mpn=mpn,pins={"1":n1,"2":n2},grp=grp)
def C(ref,val,lcsc,n1,n2,grp,fp=C0603,mpn=""):
    return dict(ref=ref,lib="Device:C",val=val,fp=fp,lcsc=lcsc,mpn=mpn,pins={"1":n1,"2":n2},grp=grp)
P=[]
# ---------------- USB-C PD input ----------------
P+=[dict(ref="J1",lib="Connector:USB_C_Receptacle_USB2.0_16P",val="USB-C IN (PD sink)",fp="Connector_USB:USB_C_Receptacle_HRO_TYPE-C-31-M-12",lcsc="C165948",mpn="HRO TYPE-C-31-M-12",grp="in",
        pins={"A4":"VBUS","A9":"VBUS","B4":"VBUS","B9":"VBUS","A1":"GND","A12":"GND","B1":"GND","B12":"GND","S1":"GND",
              "A5":"CC1","B5":"CC2","A6":None,"B6":None,"A7":None,"B7":None,"A8":None,"B8":None}),   # power-only: D+/D- not used
    dict(ref="F1",lib="Device:Fuse",val="4A 32V fast",fp="Fuse:Fuse_1206_3216Metric",lcsc="C187596",mpn="Littelfuse 0466004.NRHF",grp="in",pins={"1":"VBUS","2":"VBUS_F"}),
    dict(ref="D1",lib="Device:D_Zener",val="SMBJ22A (TVS, uni)",fp="Diode_SMD:D_SMB",lcsc="C151920",mpn="SMBJ22A",grp="in",pins={"1":"VBUS_F","2":"GND"}),
    C("C1","10uF 50V","C13585","VBUS_F","GND","in",C1206,"CL31A106KBHNNNE"),
    # HUSB238 (DS v1.0): VSET open = 20 V request, ISET 13.7k = 2.25 A; picks the highest PDO <= 20 V offering >= 2.25 A,
    # else steps down (D+/D- left open: BC1.2/Apple detection unused, PD only); GATE (open drain) pulls Q1's gate low once a contract (or default 5 V) is up, releases it on OVP.
    dict(ref="U1",lib="openald:HUSB238",val="HUSB238_002DD",fp="Package_DFN_QFN:DFN-10-1EP_3x3mm_P0.5mm_EP1.55x2.48mm",lcsc="C7471904",mpn="Hynetek HUSB238_002DD",grp="in",
        pins={"1":"VBUS_F","2":None,"3":None,"4":"CC1","5":"CC2","6":None,"7":None,"8":None,"9":"ISET","10":"PD_GATE","11":"GND"}),
    R("R1","13.7k","C22793","ISET","GND","in","0603WAF1372T5E"),
    C("C2","1uF 50V","C15849","VBUS_F","GND","in",mpn="CL10A105KB8NNNC"),
    dict(ref="Q1",lib="openald:AO4407A",val="AO4407A",fp="Package_SO:SOIC-8_3.9x4.9mm_P1.27mm",lcsc="C16072",mpn="AOS AO4407A",grp="in",
        pins={"1":"VBUS_F","2":"VBUS_F","3":"VBUS_F","4":"Q1_G","5":"VIN_SW","6":"VIN_SW","7":"VIN_SW","8":"VIN_SW"}),
    R("R2","100k","C25803","VBUS_F","Q1_G","in","0603WAF1003T5E"),     # gate pull-up to source: off by default
    R("R3","47k","C25819","Q1_G","PD_GATE","in","0603WAF4702T5E"),     # Vgs = -Vin*100/147 (13.6 V at 20 V, < 20 V max)
    C("C3","4.7nF 50V","C53987","VBUS_F","Q1_G","in",mpn="0603B472K500NT"),  # slows the turn-on (inrush into C4/C5-C8)
    dict(ref="C4",lib="Device:C_Polarized",val="100uF 35V",fp="Capacitor_SMD:CP_Elec_8x10",lcsc="C2895269",mpn="RVE100UF35V67RV0161",grp="in",pins={"1":"VIN_SW","2":"GND"})]
# ---------------- 2x SY8205FCC buck, 5.10 V (Vref 0.6 V, 75k/10k) ----------------
for s,u,base in (("A","U2",10),("B","U3",30)):
    n=lambda i: f"{i}{base+0}" if False else None
    c=lambda i: f"C{base+i}"; r=lambda i: f"R{base+i}"
    P+=[dict(ref=u,lib="openald:SY8205FCC",val="SY8205FCC",fp="Package_SO:SOIC-8-1EP_3.9x4.9mm_P1.27mm_EP2.29x3mm",lcsc="C111875",mpn="Silergy SY8205FCC",grp="buck"+s,
            pins={"1":f"BS_{s}","2":f"LX_{s}","3":f"EN_{s}","4":f"SS_{s}","5":f"FB_{s}","6":f"VCC_{s}","7":"VIN_SW","8":"VIN_SW","9":"GND"}),
        C(c(1),"10uF 50V","C13585","VIN_SW","GND","buck"+s,C1206,"CL31A106KBHNNNE"),
        C(c(2),"10uF 50V","C13585","VIN_SW","GND","buck"+s,C1206,"CL31A106KBHNNNE"),
        C(c(3),"100nF","C14663",f"BS_{s}",f"LX_{s}","buck"+s,mpn="CC0603KRX7R9BB104"),
        C(c(4),"1uF","C15849",f"VCC_{s}","GND","buck"+s,mpn="CL10A105KB8NNNC"),
        C(c(5),"22nF","C21122",f"SS_{s}","GND","buck"+s,mpn="CL10B223KB8NNNC"),
        dict(ref=f"L{1 if s=='A' else 2}",lib="Device:L",val="4.7uH 7A",fp="openald:L_Sunlord_MWSA0604S",lcsc="C408457",mpn="Sunlord MWSA0604S-4R7MT",grp="buck"+s,pins={"1":f"LX_{s}","2":f"5V_{s}"}),
        C(c(6),"22uF 25V","C45783",f"5V_{s}","GND","buck"+s,C0805,"CL21A226MAQNNNE"),
        C(c(7),"22uF 25V","C45783",f"5V_{s}","GND","buck"+s,C0805,"CL21A226MAQNNNE"),
        C(c(8),"22uF 25V","C45783",f"5V_{s}","GND","buck"+s,C0805,"CL21A226MAQNNNE"),
        dict(ref=c(9),lib="Device:C_Polarized",val="470uF 10V",fp="Capacitor_SMD:CP_Elec_6.3x7.7",lcsc="C2858856",mpn="RVT470UF10V67RV0159",grp="buck"+s,pins={"1":f"5V_{s}","2":"GND"}),
        C(c(10),"100pF","C14858",f"5V_{s}",f"FB_{s}","buck"+s,mpn="CL10C101JB8NNNC"),
        R(r(1),"75k","C23242",f"5V_{s}",f"FB_{s}","buck"+s,"0603WAF7502T5E"),
        R(r(2),"10k","C25804",f"FB_{s}","GND","buck"+s,"0603WAF1002T5E"),
        # EN divider: rising threshold 1.2-1.4 V -> 11.2-13.1 V at VIN (typ 12.1 V); off below 10.3-12.1 V.
        # 5 V and 9 V never enable the bucks; 15 V and 20 V always do; 12 V is not supported.
        R(r(3),"100k","C25803","VIN_SW",f"EN_{s}","buck"+s,"0603WAF1003T5E"),
        R(r(4),"12k","C22790",f"EN_{s}","GND","buck"+s,"0603WAF1202T5E")]
# ---------------- 6x slot switch (SY6280AAC, Ilim = 6800/Rset = 1.45 A +-25 %) + plug ----------------
for i in range(1,7):
    rail="5V_A" if i in (1,2,4) else "5V_B"
    P+=[dict(ref=f"U{3+i}",lib="openald:SY6280AAC",val="SY6280AAC",fp="Package_TO_SOT_SMD:SOT-23-5",lcsc="C55136",mpn="Silergy SY6280AAC",grp=f"slot{i}",
            pins={"1":f"SLOT{i}","2":"GND","3":f"ISET{i}","4":rail,"5":rail}),
        R(f"R{50+i}","4.7k","C23162",f"ISET{i}","GND",f"slot{i}","0603WAF4701T5E"),
        C(f"C{50+i}","1uF","C15849",rail,"GND",f"slot{i}",mpn="CL10A105KB8NNNC"),
        C(f"C{60+i}","10uF 25V","C15850",f"SLOT{i}","GND",f"slot{i}",C0805,"CL21A106KAYNNNE"),
        R(f"R{60+i}","22k","C31850",f"SLOT{i}",f"CC{i}S","slot{i}" if False else f"slot{i}","0603WAF2202T5E"),   # Rp: 'default USB power'
        dict(ref=f"J{1+i}",lib="openald:USB_C_Plug_16P",val=f"SLOT {i} plug",fp="openald:USB_C_Plug_HX_TYPE-C-M-16P_Vertical",lcsc="C55200592",mpn="HX TYPE C-M 16P V-SMT",grp=f"slot{i}",hand=True,
            pins={"A1":"GND","A12":"GND","B1":"GND","B12":"GND","S1":"GND","A4":f"SLOT{i}","A9":f"SLOT{i}","B4":f"SLOT{i}","B9":f"SLOT{i}",
                  "A5":f"CC{i}S","B5":None,"A6":None,"A7":None,"B6":None,"B7":None,"A8":None,"B8":None})]
# ---------------- status LED (light pipe in the deck between the centre pockets) ----------------
P+=[dict(ref="D2",lib="Device:LED",val="Green (5 V on)",fp="LED_SMD:LED_0603_1608Metric",lcsc="C12624",mpn="KT-0603G",grp="led",pins={"1":"GND","2":"LEDG_A"}),
    R("R4","1k","C21190","5V_A","LEDG_A","led","0603WAF1001T5E"),
    dict(ref="D3",lib="Device:LED",val="Red (no PD)",fp="LED_SMD:LED_0603_1608Metric",lcsc="C2286",mpn="KT-0603R",grp="led",pins={"1":"GND","2":"LEDR_A"}),
    R("R5","4.7k","C17673","VBUS_F","LEDR_A","led","0805W8F4701T5E",fp=R0805),
    dict(ref="Q2",lib="Transistor_FET:AO3400A",val="AO3400A",fp="Package_TO_SOT_SMD:SOT-23",lcsc="C20917",mpn="AOS AO3400A",grp="led",pins={"1":"5V_A","2":"GND","3":"LEDR_A"}),
    R("R6","100k","C25803","5V_A","GND","led","0603WAF1003T5E")]   # bleeds 5V_A so Q2 turns off (red back on) when the buck stops
# ---------------- mechanical ----------------
for i in range(1,7):
    P.append(dict(ref=f"H{i}",lib="Mechanical:MountingHole",val="M3",fp="MountingHole:MountingHole_3.2mm_M3",lcsc="",mpn="M3 screw hole",grp="mech",pins={},nobom=True,boardonly=True))
for i in range(7,19):
    P.append(dict(ref=f"H{i}",lib="Mechanical:MountingHole",val="peg",fp="MountingHole:MountingHole_2.2mm_M2",lcsc="",mpn="floor-pad locating peg hole",grp="mech",pins={},nobom=True,boardonly=True))
PARTS={p["ref"]:p for p in P}
